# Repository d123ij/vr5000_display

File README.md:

This project is to create a substitute display unit for Yaesu VR-5000 broad band receiver "famous" for failing LCDs. The design is made possible only because of prior work by kakiralime (this is youtube username). I would not have enough patience to pull this through myself. 
There are three parts to the project:
 - Hardware (PCB)
 - FPGA firmware project
 - RP2040 firmware project

1. PCB project. Pretty simple 2 layer board made with JLCPCB
2. FPGA project is to emulate functionality of NJU6575 IC used in the original LCD and pass data along to the RP2040 that does all the graphics. The vr5000 CPU does use read-modify-write approach when working with the display memory. Therefore, when the original display IC, NJU6575 is removed its buffer has to be simulated. In this project is was done using Lattce LCMXO2-1200HC FPGA ($7). The FPGA has internal flash memory and free tool set is provided from Lattice. It can be programmed using HW-USBN-2A clone from e-bay. The cheapest one at the time of this writing was around $20. In addition to simulating the memory buffer the FPGA also packages and sends data to the rp2040. Communication protocol is one-directional and uses 6 lines all from FPGA to rp2040. There are: CSN, CLK and DATA(3:0). Every transaction has three clock pulses and both edges of the clock are used for the data transfer. Two clocks are used to sent four bytes, the third clock is dummy to make sure rp2040 state machine never get stuck. There is only one command to send page and column number for data transfers. Data transactions are sent one byte per transfer. The FPGA system interface has to handle 5V, which is achieved by using 8 bit level shifter IC to deal with bi-directional data lines. WRN, RDN and A0 signals are input only and dealt with by using a current limiting resistor on the FPGA input. 
3. RP2040 is responsible for displaying data. All the graphic utilities are based on kakiralime's work. I used them pretty much unchanged. The firmware runs on top of FreeRTOS. Communication with the FPGA is done via PIO state machine. rp2040 is a slave, it monitors CSN and CLK signals and inputs data when clock transition is detected. Data are transferred from input FIFOs to memory via two chained DMA channels that operate continuously. I found that using one DMA in conjunction with interrupt is not fast enough and data are lost periodically with that approach. Chaining DMAs solved that. Once data arrived they placed in queue by ISR. One of the background tasks dequeues data and processes incoming commands and data. The data format for the LCD consumption follows the one in kakiralime work to minimize amount of work. I only updated in/out routines for a different CPU and restructured code somewhat. The utilized LCD model is the same, currently ~$10 delivered from AliExpress (I bough it from JR E-Shop). You can see the image from AliExpress in the image section. Programming of the rp2040 was done using debug interface and PI pico module as a debugger. I actually routed debugging connector out of receiver to modify software while operating radio. 
4. This project is not for faint-harted! You should be able to solder QFN packages and trap-door connectors with 0.6 mm pitch. To fit the new unit inside the receiver I reused the original plexiglass block by making a cavity large enough to fit the new PCB, which is fixed to the back of the LCD by sticky tape. Dremel tool is your friend here. The new display dimension is somewhat smaller than original LCD, you can see the space on the right side of the screen unoccupied by the LCD.
5. This design requires two power connections. The 5V power was taken from c5012 as 5v from the LCD connector is there even when the receiver is off. Backlight power was taken from TP5069. The board consumption was around 50-60mA. Backlight current was about 80mA.

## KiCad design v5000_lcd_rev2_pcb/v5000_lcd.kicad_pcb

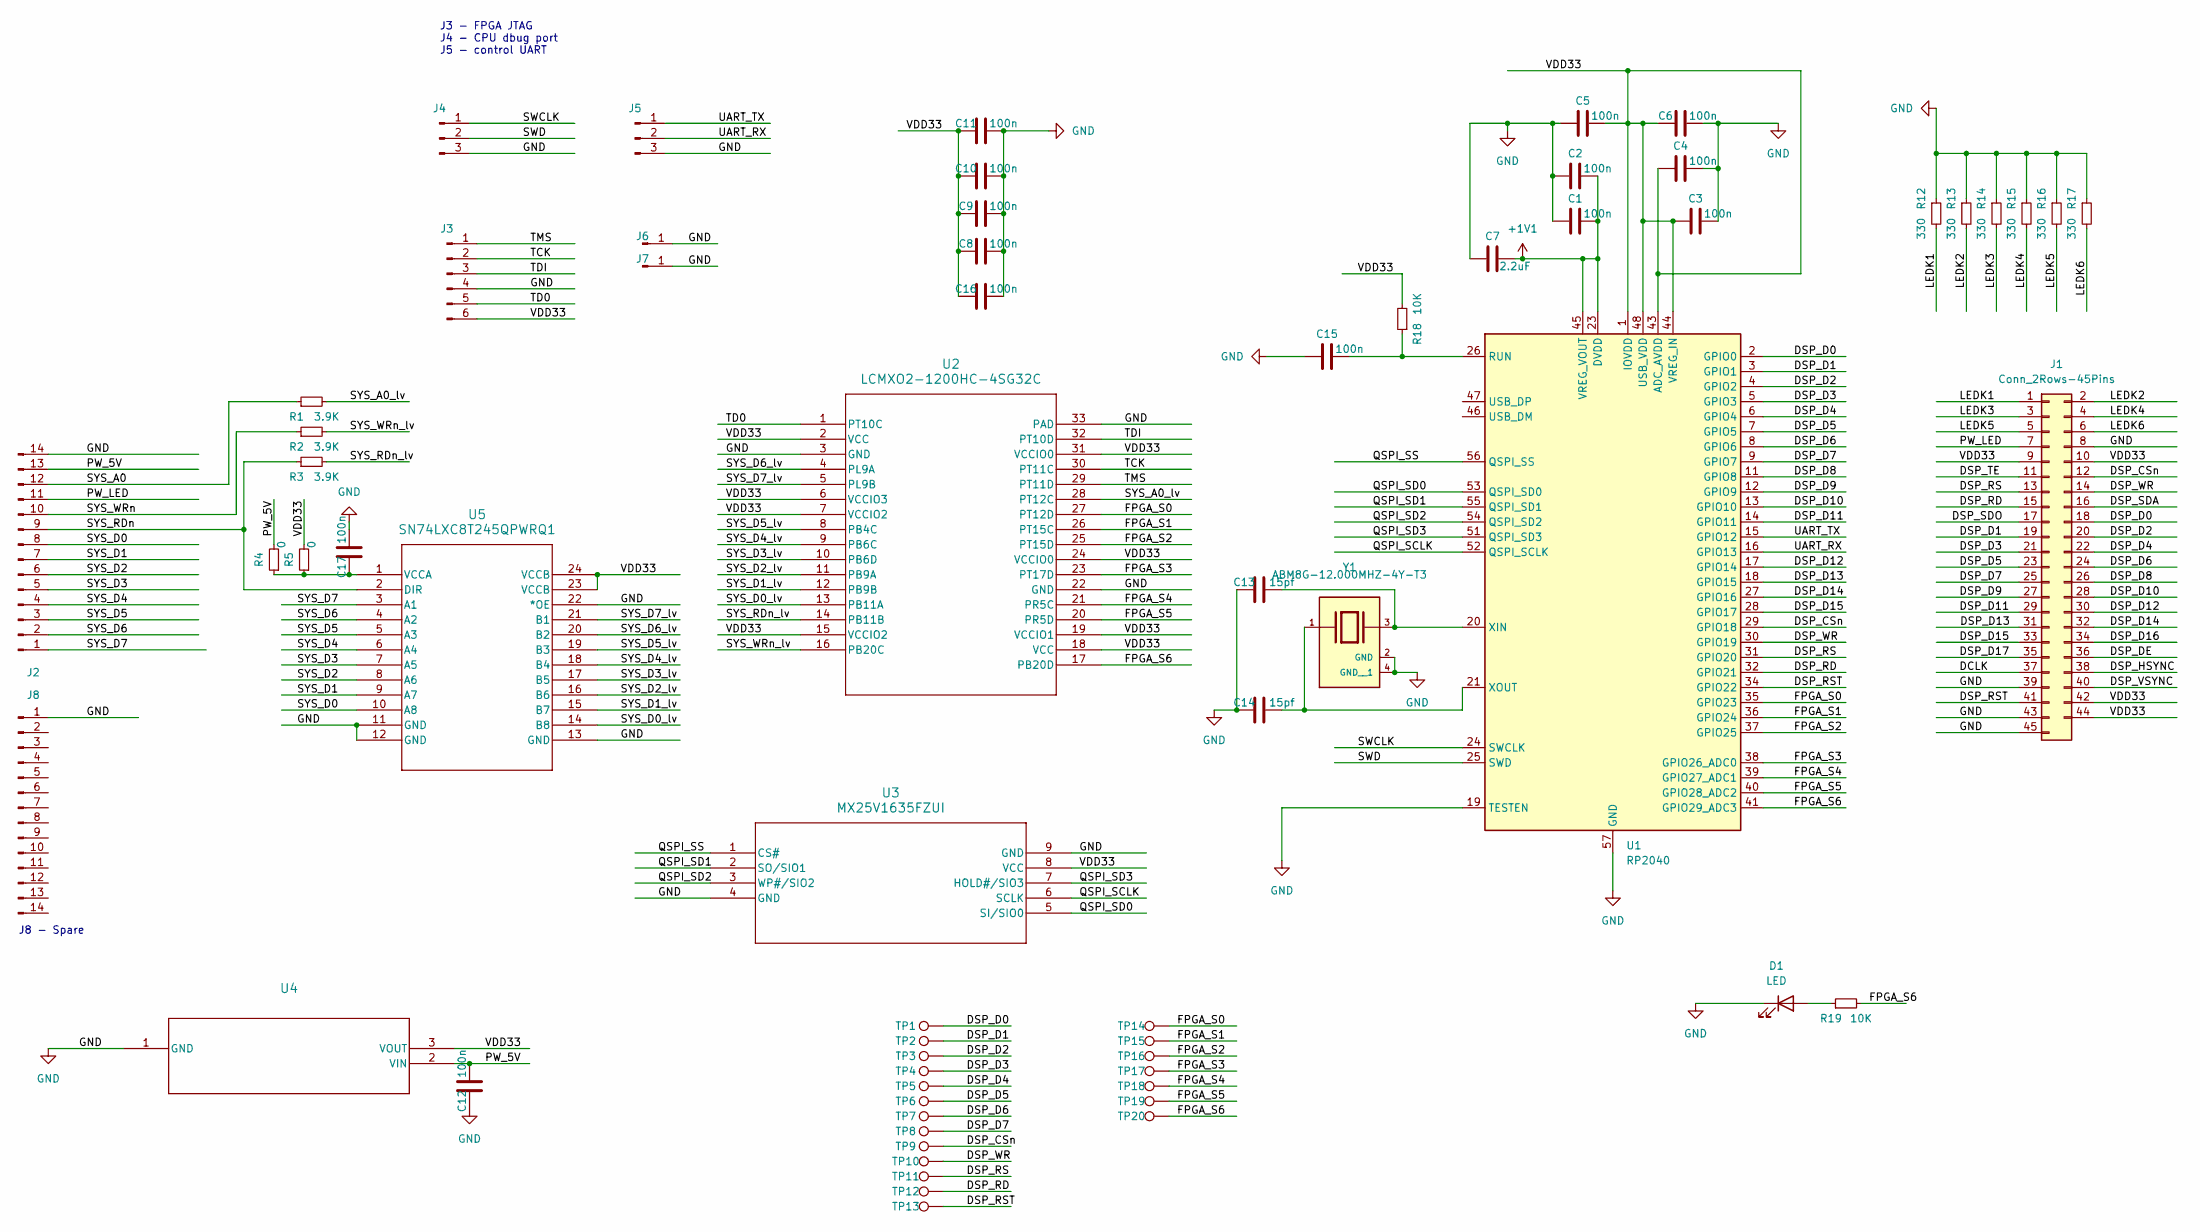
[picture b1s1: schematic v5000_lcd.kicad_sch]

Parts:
C1, C2, C3, C4, C5, C6, C8, C9, C10, C11, C12, C15, C16, C17: 100n; C_0603_1608Metric
C7: 2.2uF; C_0603_1608Metric
C13, C14: 15pf; C_0603_1608Metric
D1: LED; D_0805_2012Metric
J1: Conn_2Rows-45Pins; CONN_45_FPC_06MM
J2: Conn_01x14_Pin; CON_532611471
J3: Conn_01x06_Pin; PinHeader_1x06_P2.54mm_Vertical
J4, J5: Conn_01x03_Pin; PinHeader_1x03_P2.54mm_Vertical
J6, J7: Conn_01x01_Pin; PinSocket_1x01_P2.54mm_Vertical
J8: Conn_01x14_Pin; PinHeader_2x07_P2.54mm_Vertical
R1, R2, R3: 3.9K; R_0603_1608Metric
R4, R5: 0; R_0603_1608Metric
R12, R13, R14, R15, R16, R17: 330; R_0603_1608Metric
R18, R19: 10K; R_0603_1608Metric
TP1, TP2, TP3, TP4, TP5, TP6, TP7, TP8, TP9, TP10, TP11, TP12, TP13, TP14, TP15, TP16, TP17, TP18, TP19, TP20: TestPoint; tp_small
U1: RP2040; QFN-56-1EP_7x7mm_P0.4mm_EP3.2x3.2mm
U2: LCMXO2-1200HC-4SG32C; QFN32_SG32C_LAT
U3: MX25V1635FZUI; 8-USON_2X3_MAC
U4: MCP1700T-1202E/MB; SOT-89_3MC_MCH
U5: SN74LXC8T245QPWRQ1; TSSOP24_PW_TEX
Y1: ABM8G-12.000MHZ-4Y-T3; XTAL_ABM8G-12.000MHZ-4Y-T3; PARTREV 08.13.15

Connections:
+1V1: C1.2, C2.2, C7.2, U1.23 (DVDD), U1.45 (VREG_VOUT), U1.50 (DVDD)
/DCLK: J1.37
/DSP_CSn: J1.12, TP9.1, U1.29 (GPIO18)
/DSP_D0: J1.18, TP1.1, U1.2 (GPIO0)
/DSP_D1: J1.19, TP2.1, U1.3 (GPIO1)
/DSP_D2: J1.20, TP3.1, U1.4 (GPIO2)
/DSP_D3: J1.21, TP4.1, U1.5 (GPIO3)
/DSP_D4: J1.22, TP5.1, U1.6 (GPIO4)
/DSP_D5: J1.23, TP6.1, U1.7 (GPIO5)
/DSP_D6: J1.24, TP7.1, U1.8 (GPIO6)
/DSP_D7: J1.25, TP8.1, U1.9 (GPIO7)
/DSP_D8: J1.26, U1.11 (GPIO8)
/DSP_D9: J1.27, U1.12 (GPIO9)
/DSP_D10: J1.28, U1.13 (GPIO10)
/DSP_D11: J1.29, U1.14 (GPIO11)
/DSP_D12: J1.30, U1.17 (GPIO14)
/DSP_D13: J1.31, U1.18 (GPIO15)
/DSP_D14: J1.32, U1.27 (GPIO16)
/DSP_D15: J1.33, U1.28 (GPIO17)
/DSP_D16: J1.34
/DSP_D17: J1.35
/DSP_DE: J1.36
/DSP_HSYNC: J1.38
/DSP_RD: J1.15, TP12.1, U1.32 (GPIO21)
/DSP_RS: J1.13, TP11.1, U1.31 (GPIO20)
/DSP_RST: J1.41, TP13.1, U1.34 (GPIO22)
/DSP_SDA: J1.16
/DSP_SDO: J1.17
/DSP_TE: J1.11
/DSP_VSYNC: J1.40
/DSP_WR: J1.14, TP10.1, U1.30 (GPIO19)
/FPGA_S0: TP14.1, U1.35 (GPIO23), U2.27 (PT12D)
/FPGA_S1: TP15.1, U1.36 (GPIO24), U2.26 (PT15C)
/FPGA_S2: TP16.1, U1.37 (GPIO25), U2.25 (PT15D)
/FPGA_S3: TP17.1, U1.38 (GPIO26_ADC0), U2.23 (PT17D)
/FPGA_S4: TP18.1, U1.39 (GPIO27_ADC1), U2.21 (PR5C)
/FPGA_S5: TP19.1, U1.40 (GPIO28_ADC2), U2.20 (PR5D)
/FPGA_S6: R19.2, TP20.1, U1.41 (GPIO29_ADC3), U2.17 (PB20D)
/LEDK1: J1.1, R12.2
/LEDK2: J1.2, R13.2
/LEDK3: J1.3, R14.2
/LEDK4: J1.4, R15.2
/LEDK5: J1.5, R16.2
/LEDK6: J1.6, R17.2
/PW_5V: C12.2, J2.13, R4.2, U4.2 (VIN)
/PW_LED: J1.7, J2.11
/QSPI_SCLK: U1.52 (QSPI_SCLK), U3.6 (SCLK)
/QSPI_SD0: U1.53 (QSPI_SD0), U3.5 (SI/SIO0)
/QSPI_SD1: U1.55 (QSPI_SD1), U3.2 (SO/SIO1)
/QSPI_SD2: U1.54 (QSPI_SD2), U3.3 (WP#/SIO2)
/QSPI_SD3: U1.51 (QSPI_SD3), U3.7 (HOLD#/SIO3)
/QSPI_SS: U1.56 (QSPI_SS), U3.1 (CS#)
/SWCLK: J4.1, U1.24 (SWCLK)
/SWD: J4.2, U1.25 (SWD)
/SYS_A0: J2.12, R1.1
/SYS_A0_lv: R1.2, U2.28 (PT12C)
/SYS_D0: J2.8, U5.10 (A8)
/SYS_D0_lv: U2.13 (PB11A), U5.14 (B8)
/SYS_D1: J2.7, U5.9 (A7)
/SYS_D1_lv: U2.12 (PB9B), U5.15 (B7)
/SYS_D2: J2.6, U5.8 (A6)
/SYS_D2_lv: U2.11 (PB9A), U5.16 (B6)
/SYS_D3: J2.5, U5.7 (A5)
/SYS_D3_lv: U2.10 (PB6D), U5.17 (B5)
/SYS_D4: J2.4, U5.6 (A4)
/SYS_D4_lv: U2.9 (PB6C), U5.18 (B4)
/SYS_D5: J2.3, U5.5 (A3)
/SYS_D5_lv: U2.8 (PB4C), U5.19 (B3)
/SYS_D6: J2.2, U5.4 (A2)
/SYS_D6_lv: U2.4 (PL9A), U5.20 (B2)
/SYS_D7: J2.1, U5.3 (A1)
/SYS_D7_lv: U2.5 (PL9B), U5.21 (B1)
/SYS_RDn: J2.9, R3.1, U5.2 (DIR)
/SYS_RDn_lv: R3.2, U2.14 (PB11B)
/SYS_WRn: J2.10, R2.1
/SYS_WRn_lv: R2.2, U2.16 (PB20C)
/TCK: J3.2, U2.30 (PT11C)
/TD0: J3.5, U2.1 (PT10C)
/TDI: J3.3, U2.32 (PT10D)
/TMS: J3.1, U2.29 (PT11D)
/UART_RX: J5.2, U1.16 (GPIO13)
/UART_TX: J5.1, U1.15 (GPIO12)
/VDD33: C3.1, C4.1, C5.2, C6.1, C8.1, C9.1, C10.1, C11.1, C16.1, J1.9, J1.10, J1.42, J1.44, J3.6, R5.2, R18.2, U1.1 (IOVDD), U1.10 (IOVDD), U1.22 (IOVDD), U1.33 (IOVDD), U1.42 (IOVDD), U1.43 (ADC_AVDD), U1.44 (VREG_IN), U1.48 (USB_VDD), U1.49 (IOVDD), U2.2 (VCC), U2.6 (VCCIO3), U2.7 (VCCIO2), U2.15 (VCCIO2), U2.18 (VCC), U2.19 (VCCIO1), U2.24 (VCCIO0), U2.31 (VCCIO0), U3.8 (VCC), U4.3 (VOUT), U5.23 (VCCB), U5.24 (VCCB)
GND: C1.1, C2.1, C3.2, C4.2, C5.1, C6.2, C7.1, C8.2, C9.2, C10.2, C11.2, C12.1, C13.1, C14.1, C15.1, C16.2, C17.2, D1.1 (K), J1.8, J1.39, J1.43, J1.45, J2.14, J3.4, J4.3, J5.3, J6.1, J7.1, J8.1, R12.1, R13.1, R14.1, R15.1, R16.1, R17.1, U1.19 (TESTEN), U1.57 (GND), U2.3 (GND), U2.22 (GND), U2.33 (PAD), U3.4 (GND), U3.9 (GND), U4.1 (GND), U5.11 (GND), U5.12 (GND), U5.13 (GND), U5.22 (*OE), Y1.2 (GND), Y1.4 (GND__1)
unnamed: D1.2 (A), R19.1
unnamed: C15.2, R18.1, U1.26 (RUN)
unnamed: C13.2, U1.20 (XIN), Y1.3
unnamed: C14.2, U1.21 (XOUT), Y1.1
unnamed: C17.1, R4.1, R5.1, U5.1 (VCCA)

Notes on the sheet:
J3 - FPGA JTAG J4 - CPU dbug port J5 - control UART
J8 - Spare

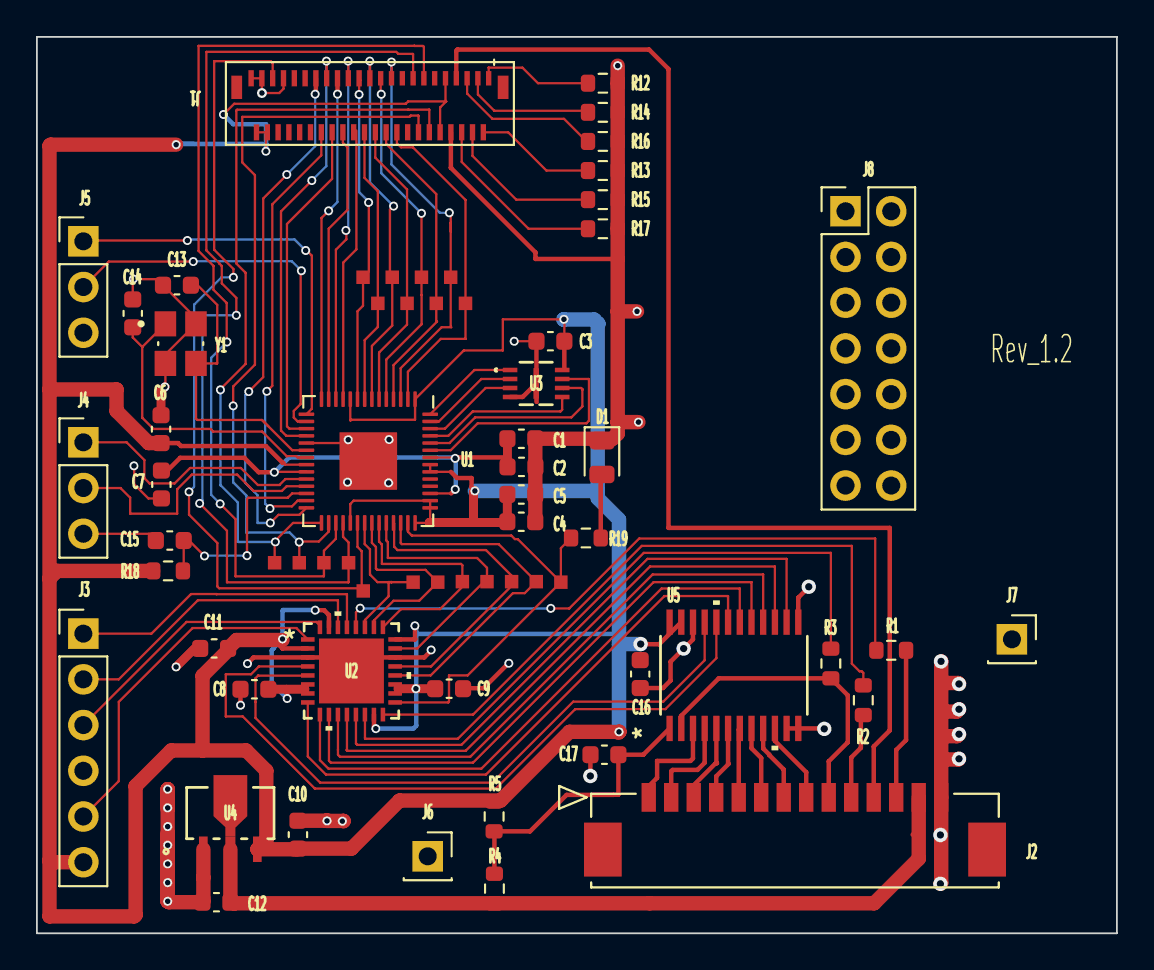
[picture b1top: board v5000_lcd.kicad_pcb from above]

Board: 2 copper layers, 60.0 x 49.8 mm, 65 parts (0 on the bottom side), 80 nets.

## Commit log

2024-02-24 Project for FPGA firmware
2024-02-24 PCB project for Yaesu vr5000 display module
2024-02-24 Added schematic PDF
2024-02-24 Adding pictures
2024-02-24 Adding original image with defective display
2024-02-25 Adding source code for rp2040 Yaesu vr5000 display project
2024-02-25 Adding AliExpress image with the LCD model
